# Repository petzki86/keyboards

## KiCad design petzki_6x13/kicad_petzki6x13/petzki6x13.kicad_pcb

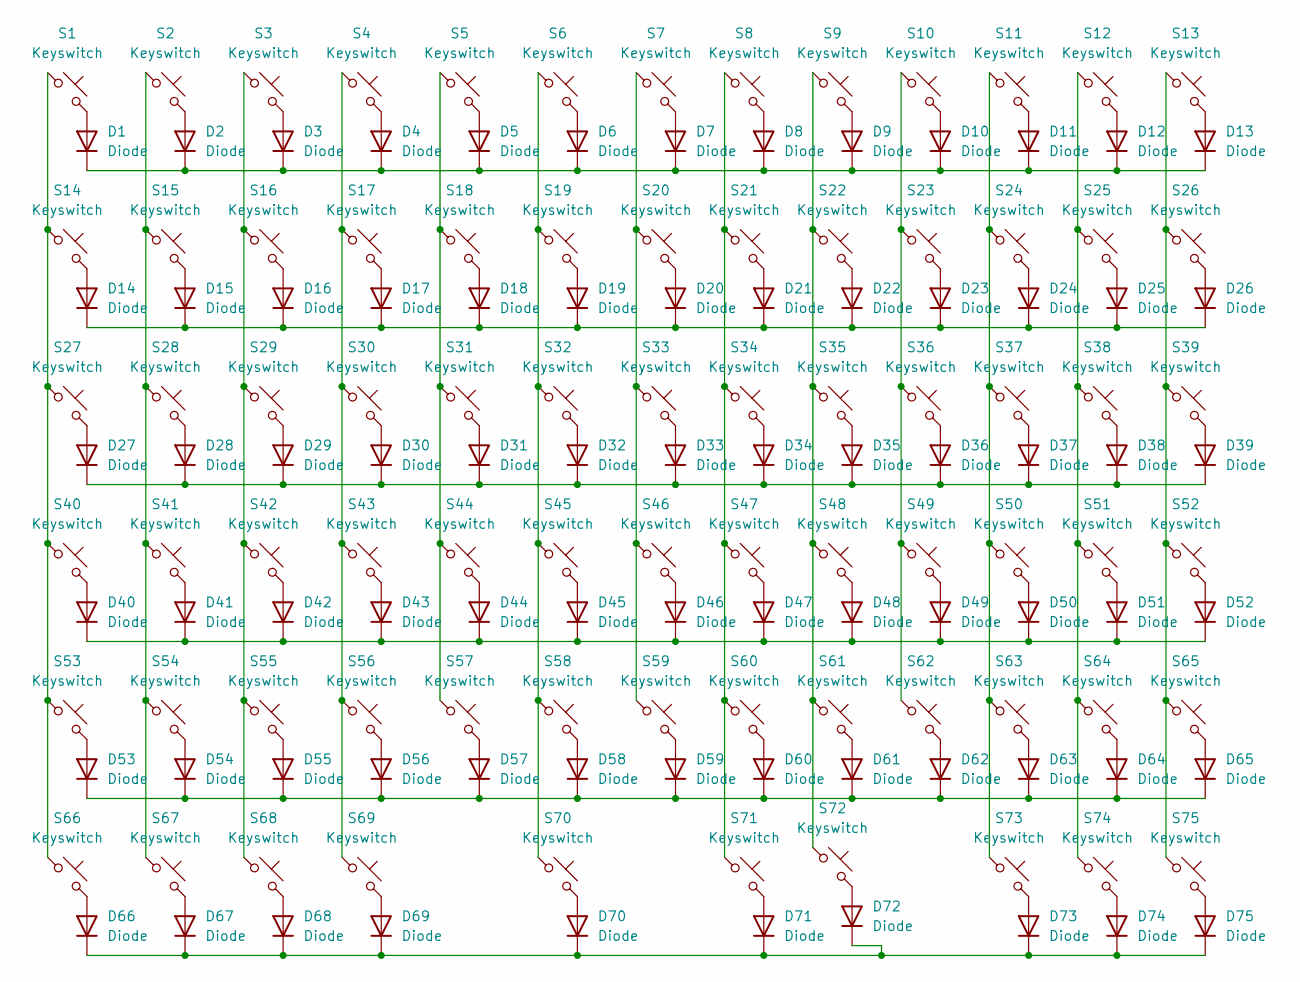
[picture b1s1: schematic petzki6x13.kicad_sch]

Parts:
D1, D2, D3, D4, D5, D6, D7, D8, D9, D10, D11, D12, D13, D14, D15, D16, D17, D18, D19, D20, D21, D22, D23, D24, D25, D26, D27, D28, D29, D30, D31, D32, D33, D34, D35, D36, D37, D38, D39, D40, D41, D42, D43, D44, D45, D46, D47, D48, D49, D50, D51, D52, D53, D54, D55, D56, D57, D58, D59, D60, D61, D62, D63, D64, D65, D66, D67, D68, D69, D70, D71, D72, D73, D74, D75: Diode; Diode_TH_SOD123
S1, S2, S3, S4, S5, S6, S7, S8, S9, S10, S11, S12, S13, S14, S15, S16, S17, S18, S19, S20, S21, S22, S23, S24, S25, S26, S27, S28, S29, S30, S31, S32, S33, S34, S35, S36, S37, S38, S39, S40, S41, S42, S43, S44, S45, S46, S47, S48, S49, S50, S51, S52, S53, S54, S55, S56, S57, S58, S59, S60, S61, S62, S63, S64, S65, S67, S68, S74, S75: Keyswitch; Hotswap_MX_1.00u
S66, S72, S73: Keyswitch; Hotswap_MX_1.25u
S69, S70, S71: Keyswitch; Hotswap_MX_1.75u

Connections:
unnamed: D1.2 (A), S1.2
unnamed: D1.1 (K), D2.1 (K), D3.1 (K), D4.1 (K), D5.1 (K), D6.1 (K), D7.1 (K), D8.1 (K), D9.1 (K), D10.1 (K), D11.1 (K), D12.1 (K), D13.1 (K)
unnamed: D2.2 (A), S2.2
unnamed: D3.2 (A), S3.2
unnamed: D4.2 (A), S4.2
unnamed: D5.2 (A), S5.2
unnamed: D6.2 (A), S6.2
unnamed: D7.2 (A), S7.2
unnamed: D8.2 (A), S8.2
unnamed: D9.2 (A), S9.2
unnamed: D10.2 (A), S10.2
unnamed: D11.2 (A), S11.2
unnamed: D12.2 (A), S12.2
unnamed: D13.2 (A), S13.2
unnamed: D14.2 (A), S14.2
unnamed: D14.1 (K), D15.1 (K), D16.1 (K), D17.1 (K), D18.1 (K), D19.1 (K), D20.1 (K), D21.1 (K), D22.1 (K), D23.1 (K), D24.1 (K), D25.1 (K), D26.1 (K)
unnamed: D15.2 (A), S15.2
unnamed: D16.2 (A), S16.2
unnamed: D17.2 (A), S17.2
unnamed: D18.2 (A), S18.2
unnamed: D19.2 (A), S19.2
unnamed: D20.2 (A), S20.2
unnamed: D21.2 (A), S21.2
unnamed: D22.2 (A), S22.2
unnamed: D23.2 (A), S23.2
unnamed: D24.2 (A), S24.2
unnamed: D25.2 (A), S25.2
unnamed: D26.2 (A), S26.2
unnamed: D27.2 (A), S27.2
unnamed: D27.1 (K), D28.1 (K), D29.1 (K), D30.1 (K), D31.1 (K), D32.1 (K), D33.1 (K), D34.1 (K), D35.1 (K), D36.1 (K), D37.1 (K), D38.1 (K), D39.1 (K)
unnamed: D28.2 (A), S28.2
unnamed: D29.2 (A), S29.2
unnamed: D30.2 (A), S30.2
unnamed: D31.2 (A), S31.2
unnamed: D32.2 (A), S32.2
unnamed: D33.2 (A), S33.2
unnamed: D34.2 (A), S34.2
unnamed: D35.2 (A), S35.2
unnamed: D36.2 (A), S36.2
unnamed: D37.2 (A), S37.2
unnamed: D38.2 (A), S38.2
unnamed: D39.2 (A), S39.2
unnamed: D40.2 (A), S40.2
unnamed: D40.1 (K), D41.1 (K), D42.1 (K), D43.1 (K), D44.1 (K), D45.1 (K), D46.1 (K), D47.1 (K), D48.1 (K), D49.1 (K), D50.1 (K), D51.1 (K), D52.1 (K)
unnamed: D41.2 (A), S41.2
unnamed: D42.2 (A), S42.2
unnamed: D43.2 (A), S43.2
unnamed: D44.2 (A), S44.2
unnamed: D45.2 (A), S45.2
unnamed: D46.2 (A), S46.2
unnamed: D47.2 (A), S47.2
unnamed: D48.2 (A), S48.2
unnamed: D49.2 (A), S49.2
unnamed: D50.2 (A), S50.2
unnamed: D51.2 (A), S51.2
unnamed: D52.2 (A), S52.2
unnamed: D53.2 (A), S53.2
unnamed: D53.1 (K), D54.1 (K), D55.1 (K), D56.1 (K), D57.1 (K), D58.1 (K), D59.1 (K), D60.1 (K), D61.1 (K), D62.1 (K), D63.1 (K), D64.1 (K), D65.1 (K)
unnamed: D54.2 (A), S54.2
unnamed: D55.2 (A), S55.2
unnamed: D56.2 (A), S56.2
unnamed: D57.2 (A), S57.2
unnamed: D58.2 (A), S58.2
unnamed: D59.2 (A), S59.2
unnamed: D60.2 (A), S60.2
unnamed: D61.2 (A), S61.2
unnamed: D62.2 (A), S62.2
unnamed: D63.2 (A), S63.2
unnamed: D64.2 (A), S64.2
unnamed: D65.2 (A), S65.2
unnamed: D66.2 (A), S66.2
unnamed: D66.1 (K), D67.1 (K), D68.1 (K), D69.1 (K), D70.1 (K), D71.1 (K), D72.1 (K), D73.1 (K), D74.1 (K), D75.1 (K)
unnamed: D67.2 (A), S67.2
unnamed: D68.2 (A), S68.2
unnamed: D69.2 (A), S69.2
unnamed: D70.2 (A), S70.2
unnamed: D71.2 (A), S71.2
unnamed: D72.2 (A), S72.2
unnamed: D73.2 (A), S73.2
unnamed: D74.2 (A), S74.2
unnamed: D75.2 (A), S75.2
unnamed: S1.1, S14.1, S27.1, S40.1, S53.1, S66.1
unnamed: S10.1, S23.1, S36.1, S49.1, S62.1
unnamed: S11.1, S24.1, S37.1, S50.1, S63.1, S73.1
unnamed: S12.1, S25.1, S38.1, S51.1, S64.1, S74.1
unnamed: S13.1, S26.1, S39.1, S52.1, S65.1, S75.1
unnamed: S2.1, S15.1, S28.1, S41.1, S54.1, S67.1
unnamed: S3.1, S16.1, S29.1, S42.1, S55.1, S68.1
unnamed: S4.1, S17.1, S30.1, S43.1, S56.1, S69.1
unnamed: S5.1, S18.1, S31.1, S44.1, S57.1
unnamed: S6.1, S19.1, S32.1, S45.1, S58.1, S70.1
unnamed: S7.1, S20.1, S33.1, S46.1, S59.1
unnamed: S8.1, S21.1, S34.1, S47.1, S60.1, S71.1
unnamed: S9.1, S22.1, S35.1, S48.1, S61.1, S72.1

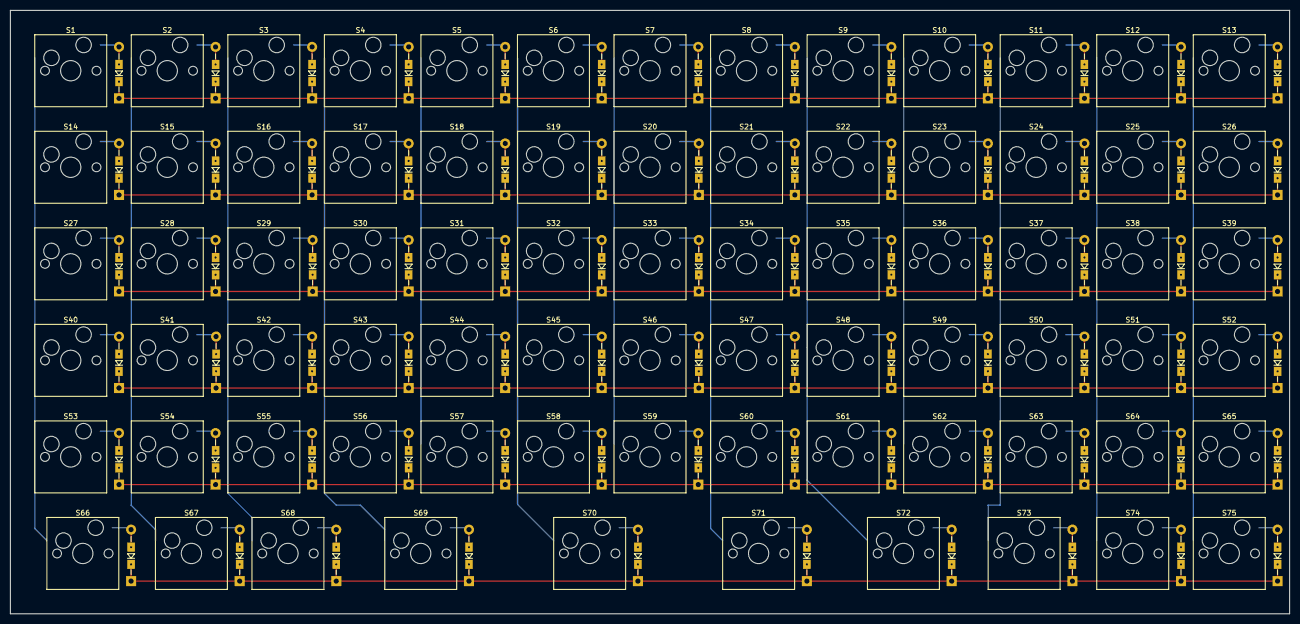
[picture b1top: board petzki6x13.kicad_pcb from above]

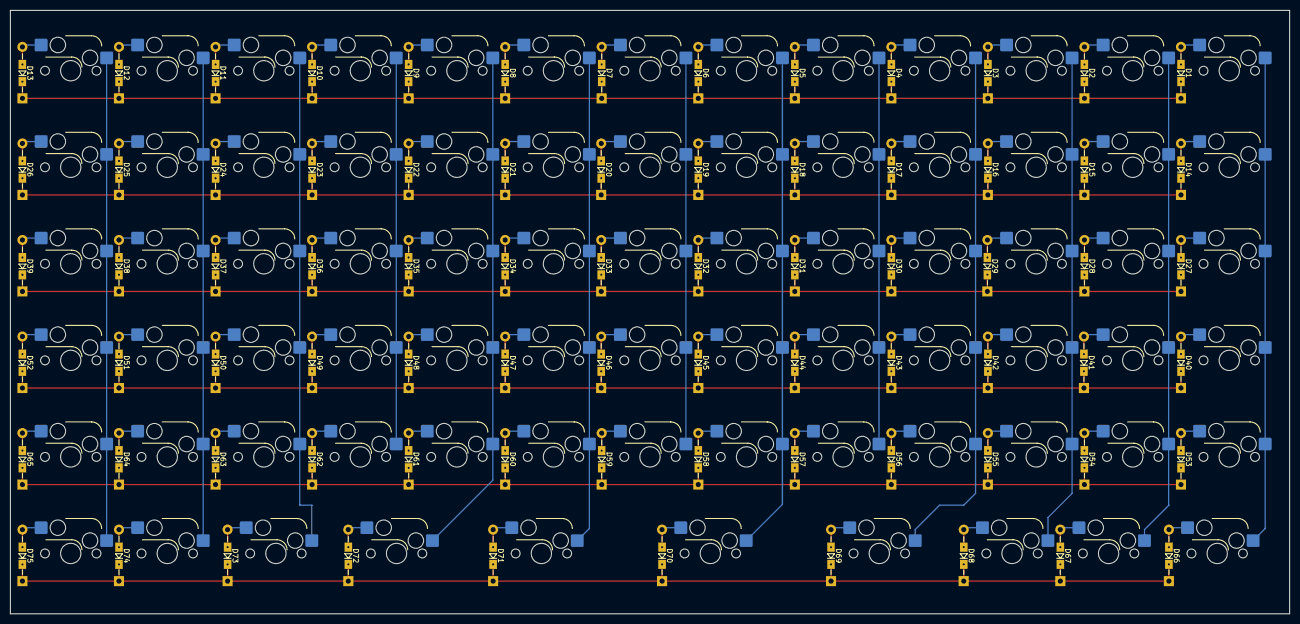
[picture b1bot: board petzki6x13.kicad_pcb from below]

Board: 2 copper layers, 252.4 x 119.1 mm, 150 parts (75 on the bottom side), 94 nets.

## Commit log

2023-11-19 Initial push
2023-11-25 Using TH-SMD diodes
2023-11-25 added edge cut zone
